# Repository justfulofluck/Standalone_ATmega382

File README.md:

# Standalone ATmega328 Arduino-Compatible Board

<div align="center">

*A minimal, cost-effective Arduino-compatible development board based on the ATmega328P microcontroller.*

</div>

---

## 📋 Overview

This project provides a complete KiCad design for a **standalone ATmega328P-based development board**. It replicates the core functionality of an Arduino Uno while eliminating unnecessary components (such as the USB-to-serial converter), making it ideal for:

- **Embedded Systems Development** – Compact footprint for permanent installations
- **IoT Prototyping** – Low-cost solution for sensor nodes and controllers
- **Production Deployment** – Ready-to-manufacture Gerber files included
- **Educational Projects** – Learn microcontroller fundamentals and PCB design

Once programmed via an external ISP programmer or Arduino-as-ISP, this board operates independently to run your Arduino sketches.

---

## ⚙️ Key Features

- **Microcontroller**: ATmega328P-PU (8-bit AVR, 32KB Flash, 2KB SRAM, 1KB EEPROM)
- **Clock Speed**: Up to 20MHz (external crystal oscillator)
- **Power Supply**: 5V regulated input
- **I/O Pins**: Full access to GPIO, ADC, PWM, UART, SPI, and I2C interfaces
- **Programming**: ISP header compatible with USBasp, AVRISP, or Arduino-as-ISP
- **Reset Button**: Manual reset push-button
- **PCB Layers**: 2-layer design with silkscreen, solder mask, and paste layers
- **Form Factor**: Compact size optimized for embedded applications

---

## 📦 Bill of Materials (BOM)

| Component | Value/Part Number | Quantity | Notes |
|-----------|------------------|----------|-------|
| U1 | ATmega328P-PU | 1 | DIP-28 package |
| Y1 | 16MHz Crystal Oscillator | 1 | External clock source |
| C1, C2 | 22pF Ceramic Capacitor | 2 | Crystal load capacitors |
| C3, C4 | 100nF Ceramic Capacitor | 2 | Power decoupling |
| R1 | 10kΩ Resistor | 1 | RESET pull-up |
| SW1 | Tactile Push Button | 1 | Reset button |
| HDR1 | 2x3 Pin Header | 1 | ISP programming header |
| HDR2, HDR3 | Female Pin Headers | 2 | I/O breakout (Arduino Uno footprint) |
| J1 | DC Power Jack / Pin Header | 1 | 5V power input |

*Note: Adjust capacitor values if using a different crystal frequency.*

---

## 🛠️ Getting Started

### Prerequisites

- **KiCad** (v7.0 or later recommended) – [Download here](https://www.kicad.org/download/)
- **ISP Programmer** – USBasp, AVRISP mkII, or Arduino board configured as ISP
- **Power Supply** – 5V regulated source (or FTDI module for serial communication)

### Installation & Compilation

1. **Clone or Download** this repository:
   ```bash
   git clone <repository-url>
   cd <project-directory>
   ```

2. **Open the Project in KiCad**:
   - Launch KiCad
   - Click **File → Open Project**
   - Select `standalone_arduino.kicad_pro`

3. **Review Schematic & PCB**:
   - Open `standalone_arduino.kicad_sch` to view/edit the schematic
   - Open `standalone_arduino.kicad_pcb` to view/edit the PCB layout

4. **Generate Manufacturing Files** (if modifications are made):
   - In PCB Editor: **File → Fabrication Outputs → Gerbers (.gbr)**
   - Generate Drill Files: **File → Fabrication Outputs → Drill Files (.drl)**

---

## 🔌 Programming the Board

Since this board lacks a built-in USB-to-serial converter, you have two options for uploading code:

### Option 1: Using an External ISP Programmer

1. Connect your ISP programmer (e.g., USBasp) to the **2x3 ISP header** on the board.
2. Select **Programmer → "USBasp"** (or your specific programmer) in Arduino IDE.
3. Choose **Tools → Board → "Arduino Uno"** (or ATmega328P variant).
4. Click **Upload Using Programmer**.

### Option 2: Arduino as ISP

1. Load the **ArduinoISP** sketch onto a standard Arduino Uno/Nano.
2. Wire the Arduino to the ISP header on this board (MISO, MOSI, SCK, RESET, VCC, GND).
3. Select **Programmer → "Arduino as ISP"** in Arduino IDE.
4. Upload your sketch using **Upload Using Programmer**.

> 💡 **Tip**: After initial programming via ISP, you can use a USB-to-TTL adapter (FTDI/CH340) connected to TX/RX pins for serial communication and bootloader-based uploads if a bootloader is installed.

---

## 📁 Project Structure

```
├── README.md                     # This documentation file
├── standalone_arduino.kicad_pro  # KiCad project file
├── standalone_arduino.kicad_sch  # Schematic design
├── standalone_arduino.kicad_pcb  # PCB layout (2-layer)
├── *.gbr                         # Gerber files for manufacturing
│   ├── standalone_arduino-F_Cu.gbr       # Front Copper
│   ├── standalone_arduino-B_Cu.gbr       # Back Copper
│   ├── standalone_arduino-F_Silkscreen.gbr
│   ├── standalone_arduino-B_Silkscreen.gbr
│   ├── standalone_arduino-F_Mask.gbr     # Front Solder Mask
│   ├── standalone_arduino-B_Mask.gbr     # Back Solder Mask
│   ├── standalone_arduino-F_Paste.gbr    # Front Solder Paste
│   ├── standalone_arduino-B_Paste.gbr    # Back Solder Paste
│   └── standalone_arduino-Edge_Cuts.gbr  # Board Outline
├── schematic_arduino-standal.avif # Schematic diagram image
├── 3D_bord_view.png              # 3D render of the PCB
├── Two_layer_scyamtics.png       # Layer visualization
└── standalone_arduino-backups/   # Automatic backup archives
```

---

## 🏭 Manufacturing Instructions

The included **Gerber files** are ready to send to any PCB fabrication service (e.g., JLCPCB, PCBWay, OSH Park).

### Recommended Specifications:
- **Board Thickness**: 1.6mm
- **Copper Weight**: 1oz (35µm)
- **Solder Mask Color**: Green (or preference)
- **Silkscreen Color**: White
- **Surface Finish**: HASL (Lead-free) or ENIG
- **Quantity**: As per your requirement (cost-effective in batches of 5+)

Simply upload the `.gbr` files (compressed into a `.zip` folder) to your manufacturer's website and select the above specifications.

---

## 🔧 Troubleshooting

| Issue | Possible Cause | Solution |
|-------|---------------|----------|
| Board not powering on | Incorrect power polarity | Verify 5V and GND connections |
| Cannot upload code | Wrong programmer selected | Ensure correct programmer is chosen in Arduino IDE |
| Microcontroller not responding | Missing/bad crystal or caps | Check oscillator circuit and solder joints |
| Reset not working | Faulty button or pull-up resistor | Test continuity of reset circuit |

---

## 🤝 Contributing

Contributions are welcome! Feel free to:
- Submit improvements to the schematic or PCB layout
- Report bugs or suggest enhancements via Issues
- Share your builds and modifications

---

## 📄 License

This project is open-source. Please refer to the LICENSE file (if included) or contact the author for usage rights.

---

## 📬 Contact & Support

For questions, suggestions, or collaboration opportunities, please open an issue in this repository or contact the project maintainer directly.

---

<div align="center">

**Happy Building! 🚀**

*Designed with KiCad | Made for Makers*

</div>

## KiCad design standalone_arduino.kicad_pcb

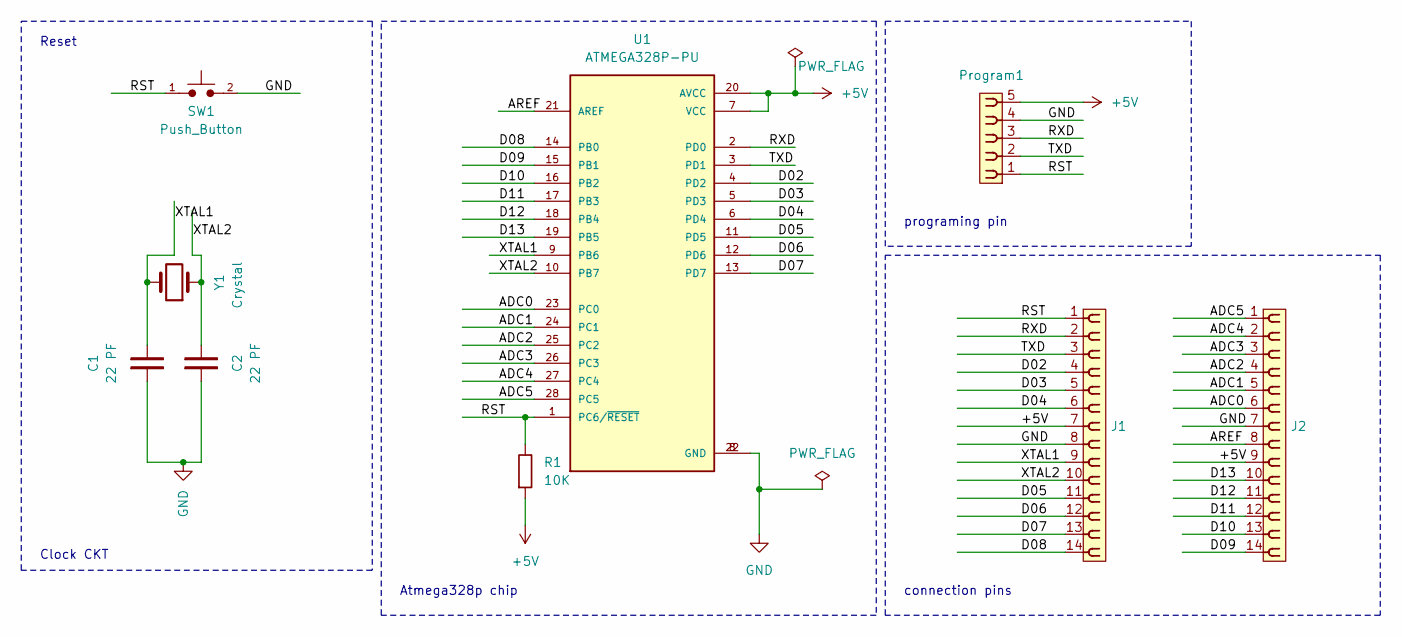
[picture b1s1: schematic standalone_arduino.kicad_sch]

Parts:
C1, C2: 22 PF; C_Disc_D5.0mm_W2.5mm_P2.50mm
J1: PINHD_1x14_Female; PinSocket_1x14_P2.54mm_Horizontal
J2: PINHD_1x14_Female; PinSocket_1x14_P2.54mm_Vertical
Program1: PINHD_1x5_Female; PinSocket_1x05_P2.54mm_Horizontal
R1: 10K; R_Axial_DIN0207_L6.3mm_D2.5mm_P10.16mm_Horizontal
SW1: Push_Button; SW_PUSH_6mm
U1: ATMEGA328P-PU; DIP794W46P254L2967H457Q28B
Y1: Crystal; Crystal_C26-LF_D2.1mm_L6.5mm_Vertical

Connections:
+5V: J1.7, J2.9, Program1.5, R1.1, U1.7 (VCC), U1.20 (AVCC)
/ADC0: J2.6, U1.23 (PC0)
/ADC1: J2.5, U1.24 (PC1)
/ADC2: J2.4, U1.25 (PC2)
/ADC3: J2.3, U1.26 (PC3)
/ADC4: J2.2, U1.27 (PC4)
/ADC5: J2.1, U1.28 (PC5)
/AREF: J2.8, U1.21 (AREF)
/D02: J1.4, U1.4 (PD2)
/D03: J1.5, U1.5 (PD3)
/D04: J1.6, U1.6 (PD4)
/D05: J1.11, U1.11 (PD5)
/D06: J1.12, U1.12 (PD6)
/D07: J1.13, U1.13 (PD7)
/D08: J1.14, U1.14 (PB0)
/D09: J2.14, U1.15 (PB1)
/D10: J2.13, U1.16 (PB2)
/D11: J2.12, U1.17 (PB3)
/D12: J2.11, U1.18 (PB4)
/D13: J2.10, U1.19 (PB5)
/RST: J1.1, Program1.1, R1.2, SW1.1, U1.1 (PC6/~RESET)
/RXD: J1.2, Program1.3, U1.2 (PD0)
/TXD: J1.3, Program1.2, U1.3 (PD1)
/XTAL1: C1.2, J1.9, U1.9 (PB6), Y1.2
/XTAL2: C2.2, J1.10, U1.10 (PB7), Y1.1
GND: C1.1, C2.1, J1.8, J2.7, Program1.4, SW1.2, U1.8 (GND), U1.22 (GND)

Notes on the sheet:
Atmega328p chip
Reset
Clock CKT
connection pins
programing pin

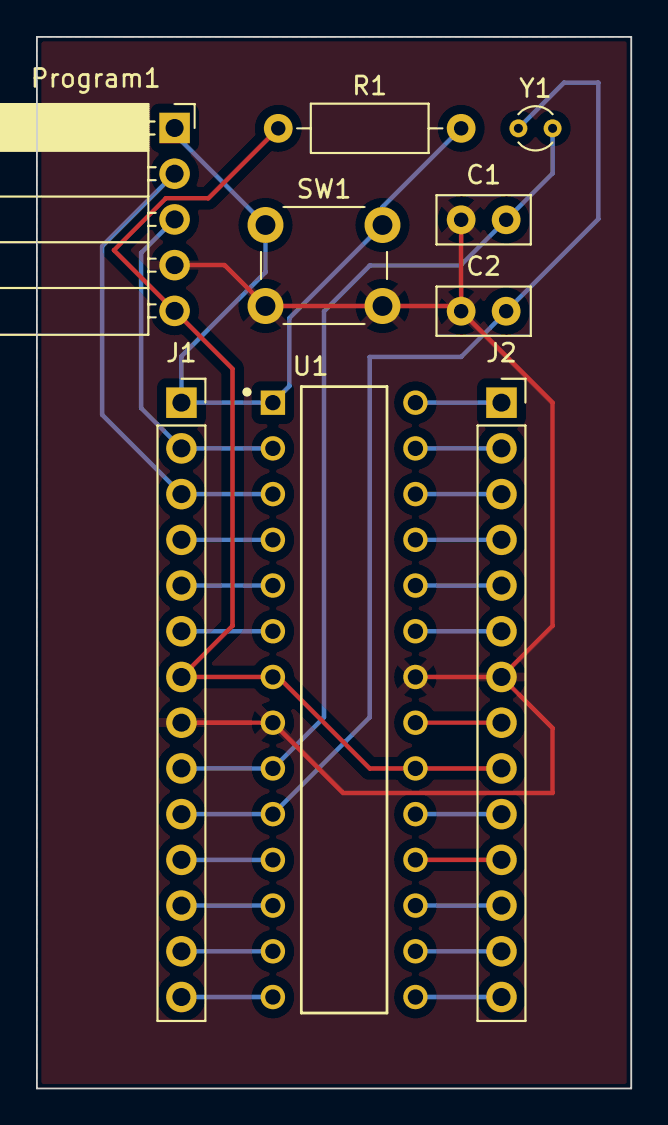
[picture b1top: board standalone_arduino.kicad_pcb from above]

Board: 2 copper layers, 33.0 x 58.4 mm, 9 parts (0 on the bottom side), 26 nets.

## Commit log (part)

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2024-03-25 schematic_degsine_upload
2024-03-25 project_gurber_files
2024-03-25 adding_backup_files
2024-03-25 adding scymatis and 3D scymatics
